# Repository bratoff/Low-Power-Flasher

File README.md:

# Low Power Flasher
Ultra low power LED flasher using ATTiny13a

Uses an ATTiny13a in ultra-low-power mode to provide a light that flashes every few seconds.
Intended to be built into other projects to provide a find-in-the-dark, power-on-reminder, etc.

The source code can be built in the Arduino environment - see Arduino folder.
It can also be built using the avr-gcc toolchain - see src folder.

The PCB schematic and board layout are available in eagle format - see eagle folder.
Finished PCBs are available from Oshpark at this link:  [https://oshpark.com/shared_projects/rQWvfmNL](https://oshpark.com/shared_projects/Jv5amJjU)

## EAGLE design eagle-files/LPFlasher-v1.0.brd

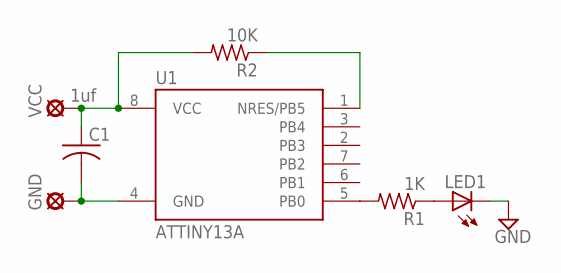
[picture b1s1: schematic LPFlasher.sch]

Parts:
C1: 1uf; C025-024X044
GND: LSP13
LED1: LED5MM
R1: 1K; 0204V
R2: 10K; 0204V
U1: ATTINY13A; PDIP08_300MIL
VCC: LSP13

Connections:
GND: C1.2, GND.MP, LED1.K (C), U1.4 (GND)
unnamed: R1.2, U1.5 (PB0)
unnamed: LED1.A, R1.1
unnamed: R2.1, U1.1 (NRES/PB5)
VCC: C1.1, R2.2, U1.8 (VCC), VCC.MP

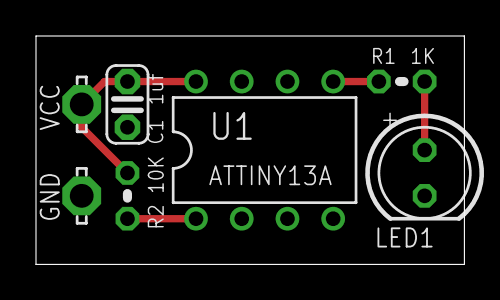
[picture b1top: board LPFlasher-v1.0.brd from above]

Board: 2 copper layers, 23.8 x 12.7 mm, 7 parts (0 on the bottom side), 5 nets.

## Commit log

2020-05-16 Update LPFlasher.ino
    Add option pins to change flash rate - see source code for details.
2020-05-17 Add v2.0 eagle files
2020-05-17 avr-gcc files
